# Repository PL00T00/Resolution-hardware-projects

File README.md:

# Week One!

For week one I made a simple LED delay device using RC timing. It uses a combination of resistors and compacitors to store and slow down the voltage into the three LED's and the slight differences in the values of these components allow for different delays in time when the LED's turn on and off.

Here's a photo!

Here's a video of me making it!

https://lapse.hackclub.com/timelapse/HAgkg-XXbsR0

Here's a link to try it out!

[https://is.gd/FY7BEo](https://www.falstad.com/circuit/circuitjs.html?ctz=DwYwlgTgBAZgvAIgIwKgFwM6IAwDpsEECsqYIiSeATAVQOx0DM2AHFQGwCcndqIARoiLZUAB0EIALI1QA3CENQBbTEICmAWiQoAfACgoUYLKgAPRC2xRLUJFRbWRsCu1QB3eAidKAhqdmKAPT6hsBuZhT2jracVI6oniLBBkYYEQiM7A42mQ5IdK7OXgjJodDmGVm2BVC5UPRUCTioCsiEJSFG4RV1DbU09XSNRUmdwAAyAKIAIumMA31UROyDw4nKAPaIACZqMD4ArgA2aBpHatt8rShQIADmzbcS3vzkXvgopUZTsxVLK30kLFVk1ilAlFsELt9sdTudLrdrnwHmCBI8lK8cB8OikJjN0kC4oCog1Qd5IdDDiczhcrhRkY80WCMW88NhPmNupEHH0bKSRjjQlyEHyhtFLGTBV0CcC+ct4gKvqAZXEbISQQLbljCNheFAwAF3gQbhhWngbrJtohGLhhPNsIxJMIOJICixXEqQOl-qt6vKJZrWfhCPRSIa2ezUKbHpbEBoqMH2JJsFxiFQqIwWLwlcKfTkBgH1p65gsxfaFestUbCDcDdrI1Bo2DYwgNHhhJx2JRGMIGJJ+xzccLyzkqoXmslgIFwBB9EA)

# Week Two!

Now this is where things start to get interesting! For week two I made a morse code machine using a monostable multivibrator (oooo long words!) Practically it works by sending a different length of voltage to an LED depending on what button you press, one for dot and one for dits. 

Here's a photo!

Here's a video of me making it!

https://lapse.hackclub.com/timelapse/-EtHCt9JcfGj

Here's a link to try it out!

[click it](https://www.falstad.com/circuit/circuitjs.html?ctz=DwYwlgTgBAZgvAIgIwKgFwM6IAwDpsEECsqYIiAzLhUkkQCxFICcRAHAGzMBMN3qIAEaIi-KAAdhCehVQA3CCNQBbTCICmAWloIAfACgoUYACUoAD0SbuLblE0UKHe9271s9xx1Txk3qADuvtgqAIbmckoA9AZGwAEWVjY8nk4uSNxsqf7BCDGGxgmWCNYZWQ5p1tgc9Nk+OHmxhYkl3NW1Fc5VBHWwDflxRUmE2fYslV71CCEDxtDFpZmji+VuIX3TqIrIBI0FwPPDNcttx9buU+vbSLuzBy3dHp0uI+fruVDbAOy3TfcL4y6XjGzEqa0uW0QN1++xADzaPTeILBFw263I03whBQUDAkUxBBxGG26zkABNEPRqK4ONhmGx3G4yvw7hh4WUXO50kttJkIRIoSplIg0BAAK7qPZxNkLU4dNYvM5lfniQVQZTChCiiVS5qy14Kx72GoQu5oB4sDjleirV42lUAOzVgnUUN26oA9ogyeoYKExQAbNDyF1WKmsRhsbAMNjcIhcNghjGaPBICjVbgcJxIG1fNrML664Dm-UUOyaG0vRH2tGocRO5CoUM7dbKL0IH1+wPBqByZsV3C00QUJhxuhfZjYehJnC4GxsL4sapIDi0ThEL6Fu6HVrtMY8uX2GsfbZEQhFoa7s6Vqplo+J2t3S8re8vO8Vh+5O4AGQAogAReFXnfBEPGPBpPW9X1-SDTQA3UMkBGuAQAHMIKECDlEEDE8GwFA7hQoCehvUCoCjU0-mfQFliQWMOkmR8-h3bQ6Jo1i3n5bYyxmJiLXYw1aLYVZURPN0YUGPihM5J5BOtT9+koyS5JBK17wo-YqNBLoBK0+xmByBSNItXTNH0sY2HjPSDM2M0+Ms0yulotwrMdZ1XRbFR207GCez7dy8CzFgfkXdM83YRgZ0xDhNwoNh9Li2gCHoL5vCfPjnKRFiMtoMQvz+QiAXYqNzOc8jGKM2UOV5VYqvAmyDGAKJwAgAwgA)

I also made a pcb for this week, its in the shape of a bird!

Here's a photo of that!

And of my schematic

# Week Three!

For week three we learnt how to use IC's so I decided to make a 555 chaser! It's quite famous in the circuitry world for how simple it is, the IC's do all the work! The 555 controls the timing and gives that information to the 4017 which can control the LED's. I also included a petentiometer which controls the resistance and changes the delay.

Here's a photo!

Here's a video of me making it!

https://lapse.hackclub.com/timelapse/mSmqghIO_AY9

Here's a 2d render of my PCB!

And here's a 3D render of my PCB!

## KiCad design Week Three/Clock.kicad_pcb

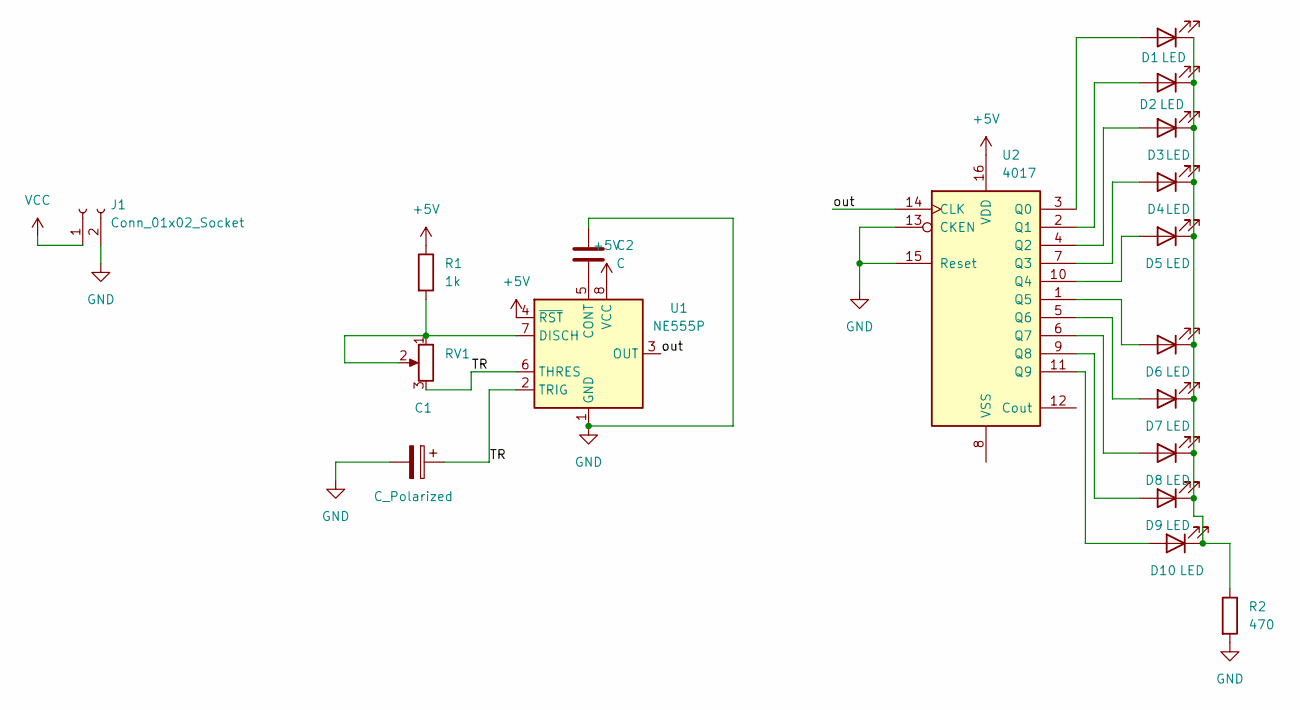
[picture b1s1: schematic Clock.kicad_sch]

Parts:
C1: C_Polarized; CP_Radial_D5.0mm_P2.00mm
C2: C; C_Disc_D7.5mm_W2.5mm_P5.00mm
D1, D2, D3, D4, D5, D6, D7, D8, D9, D10: LED; LED_D3.0mm
J1: Conn_01x02_Socket; PinHeader_1x02_P2.54mm_Vertical
R1: 1k; R_Axial_DIN0207_L6.3mm_D2.5mm_P7.62mm_Horizontal
R2: 470; R_Axial_DIN0207_L6.3mm_D2.5mm_P7.62mm_Horizontal
RV1: R_Potentiometer; Potentiometer_Vishay_T93YA_Vertical
U1: NE555P; DIP-8_W7.62mm
U2: 4017; N16

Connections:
+5V: R1.1, U1.4 (~RST), U1.8 (VCC), U2.16 (VDD)
/TR: C1.1, RV1.3, U1.2 (TRIG), U1.6 (THRES)
/out: U1.3 (OUT), U2.14 (CLK)
GND: C1.2, C2.1, J1.2, R2.2, U1.1 (GND), U2.13 (CKEN), U2.15 (Reset)
unnamed: D1.2 (A), U2.3 (Q0)
unnamed: D1.1 (K), D2.1 (K), D3.1 (K), D4.1 (K), D5.1 (K), D6.1 (K), D7.1 (K), D8.1 (K), D9.1 (K), D10.1 (K), R2.1
unnamed: D2.2 (A), U2.2 (Q1)
unnamed: D3.2 (A), U2.4 (Q2)
unnamed: D4.2 (A), U2.7 (Q3)
unnamed: D5.2 (A), U2.10 (Q4)
unnamed: D6.2 (A), U2.1 (Q5)
unnamed: D7.2 (A), U2.5 (Q6)
unnamed: D8.2 (A), U2.6 (Q7)
unnamed: D9.2 (A), U2.9 (Q8)
unnamed: D10.2 (A), U2.11 (Q9)
unnamed: C2.2, U1.5 (CONT)
unnamed: R1.2, RV1.1, RV1.2, U1.7 (DISCH)
VCC: J1.1

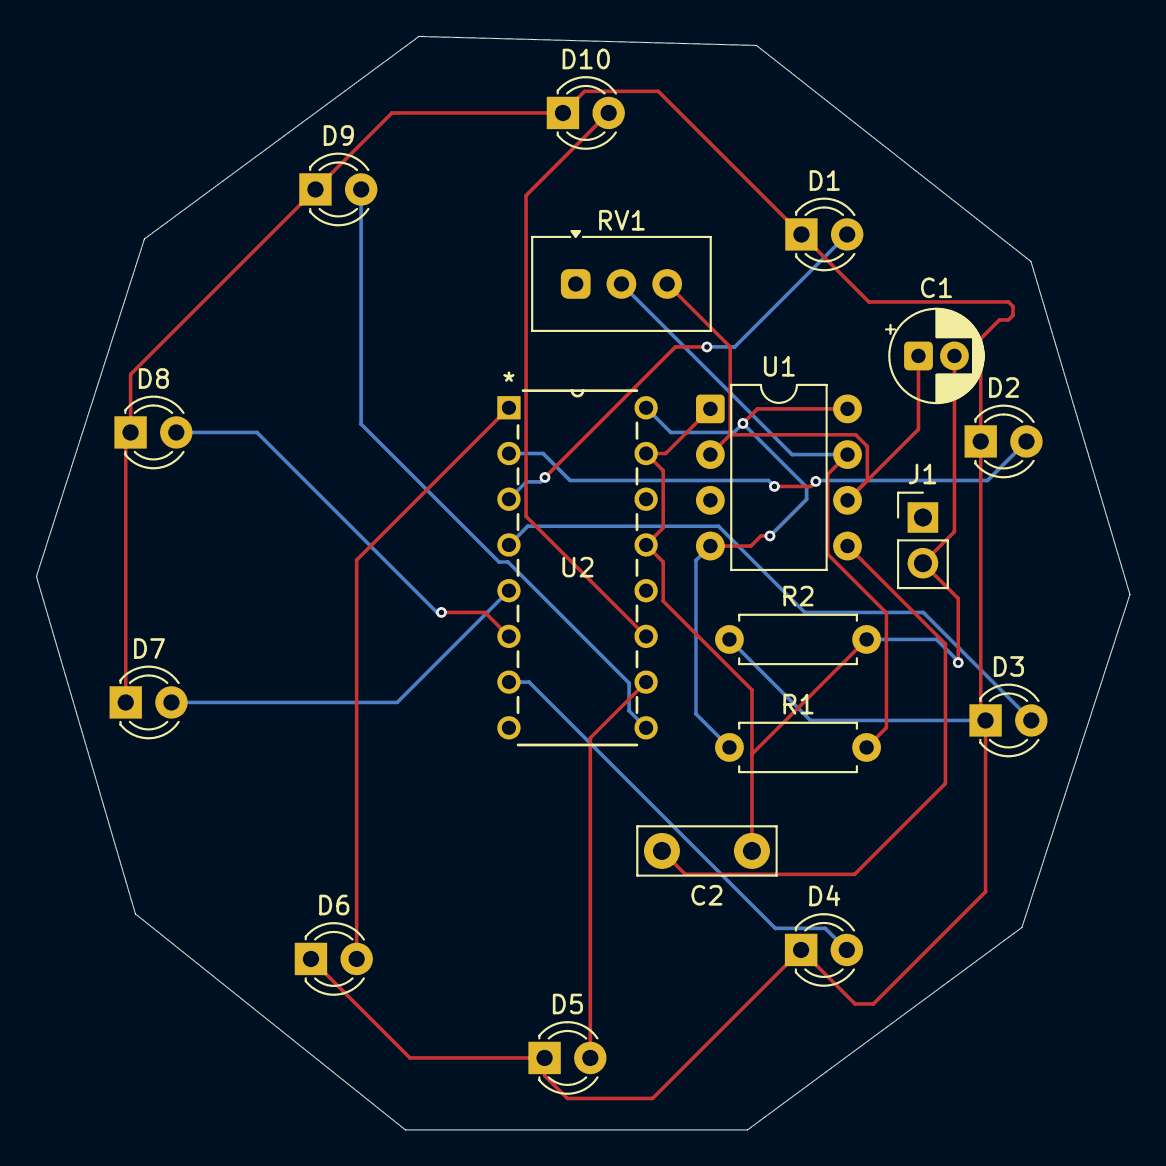
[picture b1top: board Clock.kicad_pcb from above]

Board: 2 copper layers, 60.8 x 60.8 mm, 18 parts (0 on the bottom side), 17 nets.

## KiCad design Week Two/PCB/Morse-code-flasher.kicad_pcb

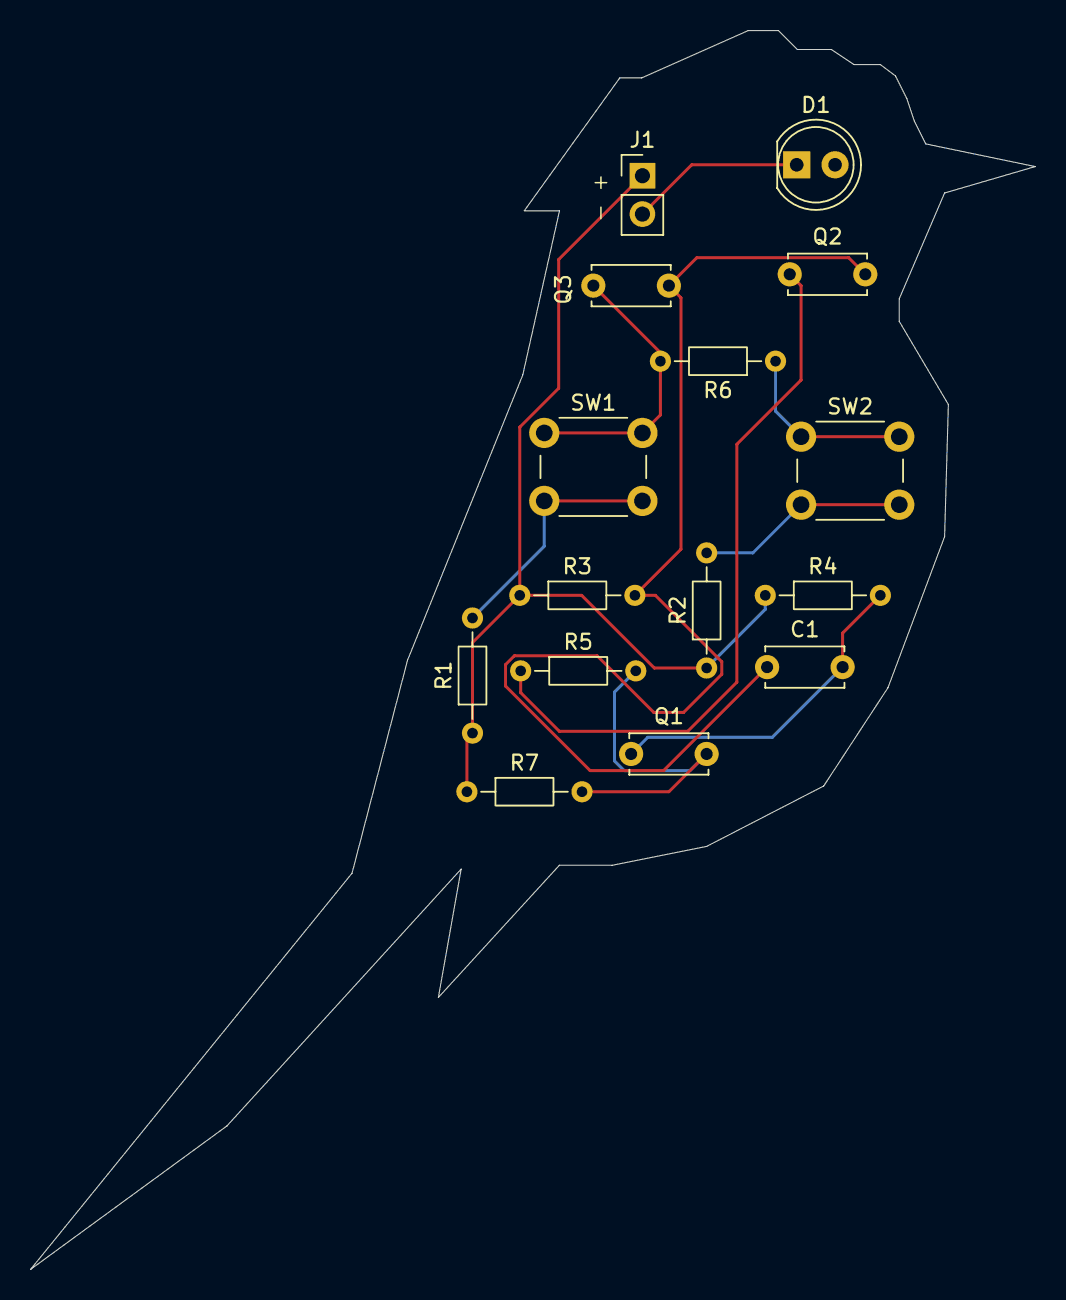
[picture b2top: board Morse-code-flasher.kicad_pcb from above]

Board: 2 copper layers, 66.5 x 82.0 mm, 15 parts (0 on the bottom side), 10 nets.

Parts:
C1: 10u; C_Disc_D5.0mm_W2.5mm_P5.00mm
D1: LED; LED_D5.0mm
J1: Conn_01x02; PinHeader_1x02_P2.54mm_Vertical
Q1, Q2, Q3: Q_NPN_BCE; C_Disc_D5.0mm_W2.5mm_P5.00mm
R1, R2: 100; R_Axial_DIN0204_L3.6mm_D1.6mm_P7.62mm_Horizontal
R3: 700; R_Axial_DIN0204_L3.6mm_D1.6mm_P7.62mm_Horizontal
R4, R5: 1k; R_Axial_DIN0204_L3.6mm_D1.6mm_P7.62mm_Horizontal
R6: 10k; R_Axial_DIN0204_L3.6mm_D1.6mm_P7.62mm_Horizontal
R7: 320; R_Axial_DIN0204_L3.6mm_D1.6mm_P7.62mm_Horizontal
SW1, SW2: SW_Push; SW_PUSH_6mm

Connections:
GND: D1.1 (K), J1.2
unnamed: C1.2, Q1.1 (B), R4.2
unnamed: Q1.2 (C), R5.2, R7.2
unnamed: Q2.1 (B), R5.1
unnamed: C1.1, Q2.2 (C), Q3.2 (C), R3.2
unnamed: Q3.1 (B), R6.2, SW1.1
unnamed: R1.2, SW1.2
unnamed: R2.2, SW2.2
unnamed: R6.1, SW2.1
VCC: J1.1, R1.1, R2.1, R3.1, R4.1, R7.1

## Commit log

2026-03-18 Updated README With Week One Details
    Added details about the week one project, including a description, image, and video link.
2026-03-18 Fixed README formatting
    Added a photo and video link for the LED delay device.
2026-03-18 Update README with video and demo links
    Added links to a video and a demo for users.
2026-03-18 Create Placeholder
2026-03-29 Added Week 2 to the README
    HEHEHE BIRB MORSE CODE HEHEHEHE
2026-03-29 Made week two folder
    AHHHHHHHHHH
2026-03-29 I forgor my schematic :(
2026-03-29 PLACEHOLDER IS STUPID
2026-03-29 Im sorry placeholder
2026-03-29 The placeholder is gonna die now
    Added a new circuit configuration with various components including resistors, wires, and a LED.
2026-03-29 I GET THE LAST LAUGH
2026-03-29 Update Lapse with video upload note
    Added note about video quality and upload limitations.
2026-04-03 Update README with week three project details
    Added details about week three project including a 555 chaser circuit, images, and a video.
2026-04-03 Create placehloolfe]tebgbvrsafzgbaer
2026-04-03 Update README with timelapse video link
    Added a link to a timelapse video of the project.
